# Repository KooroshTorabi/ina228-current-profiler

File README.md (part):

# INA228 current profiler: four revisions, from nanoamps to USB-C chargers

Open-hardware current and power meters built around TI's **INA228** 20-bit power monitor. They come in four revisions (A–D) for two jobs:

- **A, B, C: profiling microcontrollers** such as an STM32, from **deep sleep (tens of nA)** up to **full load (2.5 A)**. Three series shunts and two P-MOSFETs switch the measurement range.
- **D: USB-C power meter.** An in-line tester for chargers, phones and power banks (4–48 V, 5 A), with the analysis in a PC app.

**3D view of all four:** https://kourosh.site/ina228-current-profiler/viewer (buttons A–D at the top).

## The four revisions

| | A: integrated | B: module adapter | C: smart | D: USB-C power meter |
|---|---|---|---|---|
| |  |  |  |  |
| **Measures** | ~5 nA – 2.5 A, VIN up to ~6 V | ~5 nA – 2.5 A, VIN up to ~6 V | ~5 nA – 2.5 A, VIN 1.8–5.5 V | 7.8 µA steps – 5 A, 4–48 V |
| **Shunts / ranges** | 3 shunts, 3 ranges | 3 shunts, 3 ranges | 3 shunts, 3 ranges | 1 shunt (10 mΩ), 2 ADC ranges |
| **INA228** | on the board | off-the-shelf breakout (SparkFun or Adafruit) | on the board | on the board |
| **Who switches ranges** | your logger MCU | your logger MCU | the board (STM32G030 + comparator) | the board (STM32G0B1) |
| **Connects to** | logger MCU: I2C + 2 control lines | logger MCU: Qwiic I2C + 2 control lines | Pi / MCU / PC: I2C 0x48 or CSV over UART | PC: USB-C, serial port + browser app |
| **The host gets** | raw INA228 readings | raw INA228 readings | one number: A, V, charge, energy | V, A, W, mAh, Wh, CC/D± lines, reports |
| **Board** | 62 × 49 mm | 62 × 49 mm | 62 × 62 mm | 56 × 32 mm + USB-C plug |
| **Build** | JLCPCB assembled | adapter only, cheapest | JLCPCB assembled | JLCPCB assembled |
| **Files** | [`hardware/`](hardware) | [`hardware-module/`](hardware-module) · [notes](docs/module.md) | [`hardware-smart/`](hardware-smart) · [notes](docs/smart.md) · [firmware](firmware/smart) | [`hardware-usb/`](hardware-usb) · [notes](docs/usb.md) · [firmware](firmware/usb) · [app](https://kourosh.site/ina228-current-profiler/app/) |

## Which one to build

- **A: integrated.** You are building your own logger and want to write the ranging yourself.
  - Best for: battery-life studies of an STM32 or nRF board, controlled from your own firmware.
  - Not for: plugging into a PC and reading a number straight away; a logger MCU is needed.
- **B: module adapter.** You already have a SparkFun or Adafruit INA228 breakout, or don't want to solder a 0.5 mm-pitch chip.
  - Best for: the cheapest way to try range switching, a quick lab setup.
  - Not for: the best accuracy at nA; the sense wires to the breakout add noise and need care.
- **C: smart.** The host should just read a current: a Raspberry Pi, a test rig, a CI setup.
  - Best for: low-power profiling without writing ranging code: three ranges that look like one from nA to 2.5 A, plus exact charge and energy.
  - Not for: anything above 5.5 V or 2.5 A (A and B have the same current limit and reach about 6 V).
- **D: USB-C power meter.** Chargers, phones, power banks and cables, not microcontrollers.
  - Best for:
    - seeing what a charger negotiates (USB PD up to 48 V, PPS, QC, Apple, BC1.2) and logging a whole charge;
    - charger + cable resistance and an estimate of the battery's health, in the PC app.
  - Not for: sleep currents below about 10 µA (one 10 mΩ shunt) or SuperSpeed data (USB 2.0 is passed through).

Rough cost of D per assembled board at JLCPCB (parts, fees, shipping to the EU and VAT):
- about €20–25 each when 5 are ordered, €40–50 each for 2, and about $8–10 at 100+;
- A and C fall in the same range;
- B is cheaper, plus the breakout.

Most of the cost of a small order is JLC's fixed fees and shipping, not the parts.

## Details per revision

### A: integrated

- **On the board:** the INA228, the three shunts (50 mΩ, 1 Ω, 1 kΩ), the range MOSFETs Q1/Q2 and their gate drivers.
- **Your logger MCU:** reads the INA228 over I2C (0x40) and switches ranges with CTL_H / CTL_M. ALERT gives a fast interrupt for stepping up.
- **Connections:** VIN (J1) and DUT (J2) on 5.08 mm screw terminals, the logger on J3 (pinout [below](#logger-connector-j3-a)).
- Range table and principle: [How A–C work](#how-ac-work) · design notes: [docs/design.md](docs/design.md)

### B: module adapter

- **The adapter carries the ranging**: the shunts, range MOSFETs and gate drivers are on the adapter. The INA228 is on the breakout.
- **J4 is a Kelvin sense output**:
  - S+ is taken from the R1 pad, S− from the DUT terminal.
  - Wire S+ to the module's IN+, S− to IN− (and VBUS), GND to GND.
  - **No load current flows through the module.**
- **I2C:** the module's Qwiic connector goes to the logger. The adapter's J3 has only `3V3, GND, CTL_H, CTL_M`.

> **⚠ Disable the module's own shunt first.** Otherwise it sits directly across S+ and S−, almost all of the current goes through the sense wires, and every range reads wrong.
> - **SparkFun Current Sensor INA228 (SEN-31438):** open the **SHUNT** jumper on the back.
> - **Adafruit INA228 (5832):** remove the 15 mΩ shunt resistor.
>
> Before wiring, measure the resistance between the module's IN+ and IN−. It must be high (hundreds of kΩ or more), not milliohms.

Keep the S+/S− wires short (under 15 cm) and twisted, and away from the J1–J2 current path. Full preparation and wiring notes: [docs/module.md](docs/module.md).

### C: smart (on-board ranging)

- **One value out:**
  - I2C: read a `float` at register 0x04 of address 0x48.
  - UART: each line is `t_us,current_A,voltage_V,range`.
  - The board also integrates **charge and energy** at the full conversion rate. Average current between two reads = Δcharge / Δtime, exact even with slow polling.
- **Fast up-ranging in hardware:**
  - A TLV7021 comparator watches the drop across the shunts (threshold ≈ 32 mV).
  - When the DUT wakes up, it interrupts the MCU, which steps up a range in about 1 µs.
  - Down-ranging is done in firmware with hysteresis, so ranges never oscillate.
- **Supply:** VIN 1.8–5.5 V. 3V3 for the board comes from the host header.
- **Programming:** SWD pads (J4) for an ST-Link, such as the one on a Nucleo board.
- Details: [docs/smart.md](docs/smart.md) · firmware and register map: [firmware/smart](firmware/smart)

### D: USB-C power meter

- **Hardware:** a USB-C plug (J1) goes into the charger, the device's cable goes into the receptacle (J2), and a second USB-C port (J3) goes to the PC.
- **Measures:** V, A, W, mAh and mWh, plus the CC1/CC2/D+/D− line voltages (Type-C current advertisement, VCONN, QC/Apple/BC1.2 levels).
- **No display:** everything goes to the PC over USB as a serial port.
- **Range:** 10 mΩ shunt. ±4 A in 7.8 µA steps, switching automatically to ±16 A above 3.8 A. Board limit 5 A.
- **USB PD 3.1 EPR (48 V):** the INA228 (85 V) and the 51 V TVS cover it. The plug is rated 20 V, see [docs/usb.md](docs/usb.md#will-usb-pd-31-48-v-damage-it).
- **Pass-through:** CC1, CC2, D+, D−, SBU1 and SBU2 go straight through, so PD/QC negotiation and e-marked cables work as with the cable alone. SuperSpeed lines are not passed (USB 2.0 data at most).
- **Programming:** STM32G0B1 with TinyUSB, flashed over USB (ST DFU bootloader). No programmer needed.
- **PC app:** https://kourosh.site/ina228-current-profiler/app/ opens in Chrome or Edge and talks to the meter over Web Serial, with nothing to install.
  - Live V/A/W charts, and what the charger negotiates (USB PD level, PPS, QC, Apple, BC1.2).
  - A charge-session report: phases, voltage levels, charger + cable resistance, and an estimate of the battery's capacity and health.
  - A demo session; it also opens CSV logs. Source: [`docs/app/index.html`](docs/app/index.html).
- Details: [docs/usb.md](docs/usb.md) · firmware and commands: [firmware/usb](firmware/usb)

## How A–C work

```
VIN ──R1 50mΩ──●──R2 1Ω──●──R3 1kΩ──● DUT_VDD ──► STM32 (DUT)
               │ NODE_A  │ NODE_B   │
               │         └── Q2 ────┤   Q2 bypasses R3        (mid range)
               └────────── Q1 ──────┘   Q1 bypasses R2 + R3   (high range)

INA228: IN+ = VIN (R1 pad), IN- = DUT_VDD (DUT terminal)  → always measures the whole chain
```

| Range | FETs on | Total shunt | INA228 ADCRANGE | Full scale | Useful span |
|---|---|---|---|---|---|
| L | none | ≈ 1001 Ω | 1 (±40.96 mV) | ≈ 40 µA | ~5 nA – 35 µA |
| M | Q2 | ≈ 1.05 Ω | 1 (±40.96 mV) | ≈ 38 mA | 20 µA – 35 mA |
| H | Q1 | ≈ 60 mΩ | 0 (±163.84 mV) | > 2.5 A | 20 mA – 2.5 A |

Q1 bypasses R2 and R3 together, so at high current only **one** MOSFET's Rds(on) sits in the path.

### Why not just change a breakout's shunt?

A single shunt only moves the measurement window; it does not widen it:

| Single shunt | Full scale (±40.96 mV range) | 1 LSB | Good for |
|---|---|---|---|
| 15 mΩ (stock) | 2.7 A | ≈ 5 µA | run mode |
| 1 Ω | 41 mA | ≈ 78 nA | light run, stop modes |
| 1 kΩ | 41 µA | ≈ 78 pA | deep sleep only |

Measuring an STM32 from deep sleep (tens of nA) up to full load (2.5 A) takes switched ranges. B adds them in front of a ready-made breakout.

See [docs/design.md](docs/design.md) for the design notes: wake-up transients, leakage, calibration and firmware strategy.

## How D works

```
charger ──► J1 (USB-C plug) ══ R1 10 mΩ ══ J2 (USB-C receptacle) ──► cable ──► phone / device
                     │   CC1 CC2 D+ D- SBU1 SBU2 wired straight through   │
                     └── U1 INA228 (I, V) ── U2 STM32G0B1 ── J3 USB-C ──► PC (USB serial)
```

| INA228 range | Full scale | 1 LSB | Used |
|---|---|---|---|
| ADCRANGE 1 (±40.96 mV) | ±4.096 A | 7.8 µA | below 3.8 A (back below 3.0 A) |
| ADCRANGE 0 (±163.84 mV) | ±16.4 A | 31 µA | above 3.8 A |

- **Power:** U1 and U2 are powered from the PC's USB (J3), never from the device under test.
- **Line monitors:** CC1, CC2, D+ and D− are read through 1 MΩ / 1 MΩ dividers, about 2 MΩ of load on each line.
- **Ground:** the PC's ground and the charger's ground are joined on the board, as with any USB tester connected to a PC.

## 3D models

**Interactive viewer:** https://kourosh.site/ina228-current-profiler/viewer. Buttons A–D switch the board; turn it, zoom, and point at a part to see its name and value. Direct links: [`?v=integrated`](https://kourosh.site/ina228-current-profiler/viewer/index.html?v=integrated) · [`?v=module`](https://kourosh.site/ina228-current-profiler/viewer/index.html?v=module) · [`?v=smart`](https://kourosh.site/ina228-current-profiler/viewer/index.html?v=smart) · [`?v=usb`](https://kourosh.site/ina228-current-profiler/viewer/index.html?v=usb).

**STL in GitHub's own 3D viewer:** click a file and GitHub shows a rotatable model (one colour, no copper or silkscreen):
- [`hardware/3d/current_meter.stl`](hardware/3d/current_meter.stl) (A)
- [`hardware-module/3d/current_adapter.stl`](hardware-module/3d/current_adapter.stl) (B)
- [`hardware-smart/3d/current_smart.stl`](hardware-smart/3d/current_smart.stl) (C)
- [`hardware-usb/3d/current_usb.stl`](hardware-usb/3d/current_usb.stl) (D)

| A, bottom | B, bottom | C, bottom | D, bottom |
|---|---|---|---|
|  |  |  |  |

- **STEP** (`hardware*/3d/*.step`): opens in any CAD tool (FreeCAD, Fusion, SolidWorks) for enclosure design.
- **STL** (`hardware*/3d/*.stl`): one-colour mesh in mm, shown by GitHub and accepted by any slicer or mesh tool.
- **GLB** (`hardware*/3d/*.glb`): the same model with copper, solder mask and silkscreen from the real board layers. Opens in any glTF viewer (Blender, online glTF viewers).
- **Parts:** 3D bodies come from the KiCad 3D library. D's USB-C connectors have no library model, so `tools/add_usb_bodies.py` adds simple bodies for them.
- **Terminals (A–C):** the wire entries of J1 and J2 face the board edge.

## PCB

| A, top | B, top | C, top | D, top |
|---|---|---|---|
|  |  |  |  |

Bottom layers: `docs/*/pcb_bottom.svg`. Schematics: `hardware*/schematic.pdf` and `docs/*/schematic.svg`.

- **Boards:** all 2 layers, 1 oz copper, GND pour on both layers.
  - A and B: 62 × 49 mm. C: 62 × 62 mm. Both with 4 × M3 holes.
  - D: 56 × 32 mm plus the paddle that carries the USB-C plug. No holes.
- **Connectors:**
  - A–C: 5.08 mm screw terminals for VIN (J1) and DUT (J2), with the wire entries facing the board edge.
  - D: USB-C plug (in), USB-C receptacle (out), USB-C receptacle (PC).
- **Hand-routed nets (A–C):** the measurement-critical nets (VIN, NODE_A, NODE_B, DUT_VDD) are routed in `tools/gen_pcb.py` and locked:
  - The 2.5 A path is 2 mm wide.
  - IN+ / S+ is a Kelvin trace from the R1 pad.
  - IN− / S− is a Kelvin trace from the DUT terminal.
  - The gate pull-ups tap VIN upstream of the sense point.
  - C: the comparator's VIN feed and its IN+ line from DUT_VDD are hand-routed too.
- **Hand-routed nets (D)**, in `tools/gen_pcb_usb.py`:
  - The 5 A paths (VBUS_IN, VBUS_OUT) are 2 mm buses. The plug's four VBUS pins are joined through vias.
  - The Kelvin taps from R1 go to the INA228.
  - The paired VBUS and D+/D− pads of the receptacles are joined.
- **Autorouted nets:** everything else is routed with Freerouting.
- **Checks:** for every board, DRC is clean, nothing is unconnected, and every footprint is linked to its schematic symbol.
  - The one remaining DRC note on D is inside the JAE plug's own footprint: its shell pads sit about 0.2 mm from its own paddle edge.
- **Fabrication:** `fab/gerbers.zip` (Gerbers + drill) and `fab/positions_top.csv` in each hardware folder.

## Ordering assembled boards

A, C and D are ready to order fully assembled from JLCPCB: Gerbers, BOM with LCSC part numbers, and the pick-and-place file are in [`hardware/jlcpcb/`](hardware/jlcpcb), [`hardware-smart/jlcpcb/`](hardware-smart/jlcpcb) and [`hardware-usb/jlcpcb/`](hardware-usb/jlcpcb). B is a plain adapter: order the bare PCB from `hardware-module/fab/` and solder it by hand, or adapt `tools/jlcpcb.py`.

Settings, part list, fallback parts and what to check in the placement preview: [docs/ordering.md](docs/ordering.md).

**For D, before ordering:**
- Set the PCB thickness to what the JAE plug needs.
- JLC may not place J1 (pads on both layers); it can then be soldered by hand.

Both are explained in [docs/usb.md](docs/usb.md#before-ordering).

## Repository layout

```
hardware/            A: KiCad project, fab/, 3d/, jlcpcb/, schematic.pdf, BOM.csv
hardware-module/     B: same structure (no jlcpcb/)
hardware-smart/      C: same structure
hardware-usb/        D: same structure
docs/
  design.md          A–C design notes and calibration procedure
  module.md          B: preparing and wiring the breakout
  smart.md           C: on-board ranging, comparator, sample rate
  usb.md             D: USB-C power meter, PD 3.1 limits, pass-through, PC app, board notes
  ordering.md        ordering A, C and D assembled (JLCPCB)
  integrated/ module/ smart/ usb/  schematic, PCB and 3D renders
  viewer/            interactive 3D viewer (served at kourosh.site)
  app/               D's PC app: live charts and charge reports in the browser (Web Serial)
firmware/
  smart/             C firmware (STM32G030, bare metal) + host scripts for Pi / PC
  usb/               D firmware (STM32G0B1, TinyUSB CDC) + host/meter.py
tools/
  gen_schematic.py   schematic, symbol library and BOM   (arg: integrated | module | smart | usb)
  gen_pcb.py         A–C placement + hand-routing of the critical nets
  gen_pcb_usb.py     D placement, board outline with the plug paddle, 5 A paths and Kelvin taps
  route.py           Freerouting for the remaining nets, GND pours, DRC-gated retries
  step2glb.py        STEP → GLB with colours (OpenCascade)
  make_3d.py         adds copper/mask/silk textures to the GLB
  add_usb_bodies.py  simple 3D bodies for D's USB-C connectors
  render_3d.py       PNG renders of the GLB
  glb2stl.py         one-colour STL for GitHub's 3D viewer
  build_pcb.sh       runs all of the above and exports fab files
  jlcpcb.py          JLCPCB BOM + CPL for assembled boards   (arg: integrated | smart | usb)
```

## Host connections

### Logger connector (J3), A

| Pin | Signal | Notes |
|---|---|---|
| 1 | +3V3 | supplies the INA228 |
| 2 | GND | common ground with the DUT |
| 3 | SDA | INA228 at I2C address 0x40 |
| 4 | SCL | |
| 5 | ALERT | open drain; use as an interrupt for fast up-ranging |
| 6 | CTL_H | HIGH = Q1 on (high range). Pulled HIGH at reset |
| 7 | CTL_M | HIGH = Q2 on (mid range). Pulled HIGH at reset |

### B, C and D

- **B:** J3 is pins 1, 2, 6 and 7 of the list above, in that order. Its J4 is S+, S−, GND.
- **C:** J3 is `3V3, GND, SDA, SCL, TX, RX`: I2C slave 0x48 and UART 921600 8N1. See [firmware/smart](firmware/smart#host-interfaces-j3).
- **D:** J3 is a USB-C port. Use any USB-C or USB-A-to-C cable to the PC.
  - It shows up as a serial port (VID:PID 1209:0001) and needs no driver.
  - Data and commands: [firmware/usb](firmware/usb#output).

## Status

| | Schematic | PCB | 3D | JLCPCB files | Firmware | Fabricated / tested |
|---|---|---|---|---|---|---|
| A | ✓ | ✓ | ✓ | ✓ | logger firmware not written yet | not yet |
| B | ✓ | ✓ | ✓ | (bare PCB) | same as A | not yet |
| C | ✓ | ✓ | ✓ | ✓ | ✓ compiles, not yet run | not yet |
| D | ✓ | ✓ | ✓ | ✓ | ✓ compiles, not yet run · PC app tested with its demo | not yet |

Open work: logger firmware for A/B, and calibration and validation of every revision against a reference meter.

## Rebuilding

The schematics, PCBs and 3D files are all generated from scripts:

```sh
# needs KiCad 7+ with footprint and 3D libraries, Java, xvfb-run and the Freerouting 1.9 jar;
# the 3D step also needs: pip install cadquery-ocp trimesh pillow pyrender "pyopengl==3.1.7"
tools/build_pcb.sh /path/to/freerouting-1.9.0.jar integrated   # A
tools/build_pcb.sh /path/to/freerouting-1.9.0.jar module       # B
tools/build_pcb.sh /path/to/freerouting-1.9.0.jar smart        # C
tools/build_pcb.sh /path/to/freerouting-1.9.0.jar usb          # D
python3 tools/jlcpcb.py integrated     # JLCPCB BOM + CPL for A
python3 tools/jlcpcb.py smart          # ... for C
python3 tools/jlcpcb.py usb            # ... for D
make -C firmware/smart                 # C firmware (arm-none-eabi-gcc)
make -C firmware/usb                   # D firmware (fetches TinyUSB 0.18.0 with git)
```

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
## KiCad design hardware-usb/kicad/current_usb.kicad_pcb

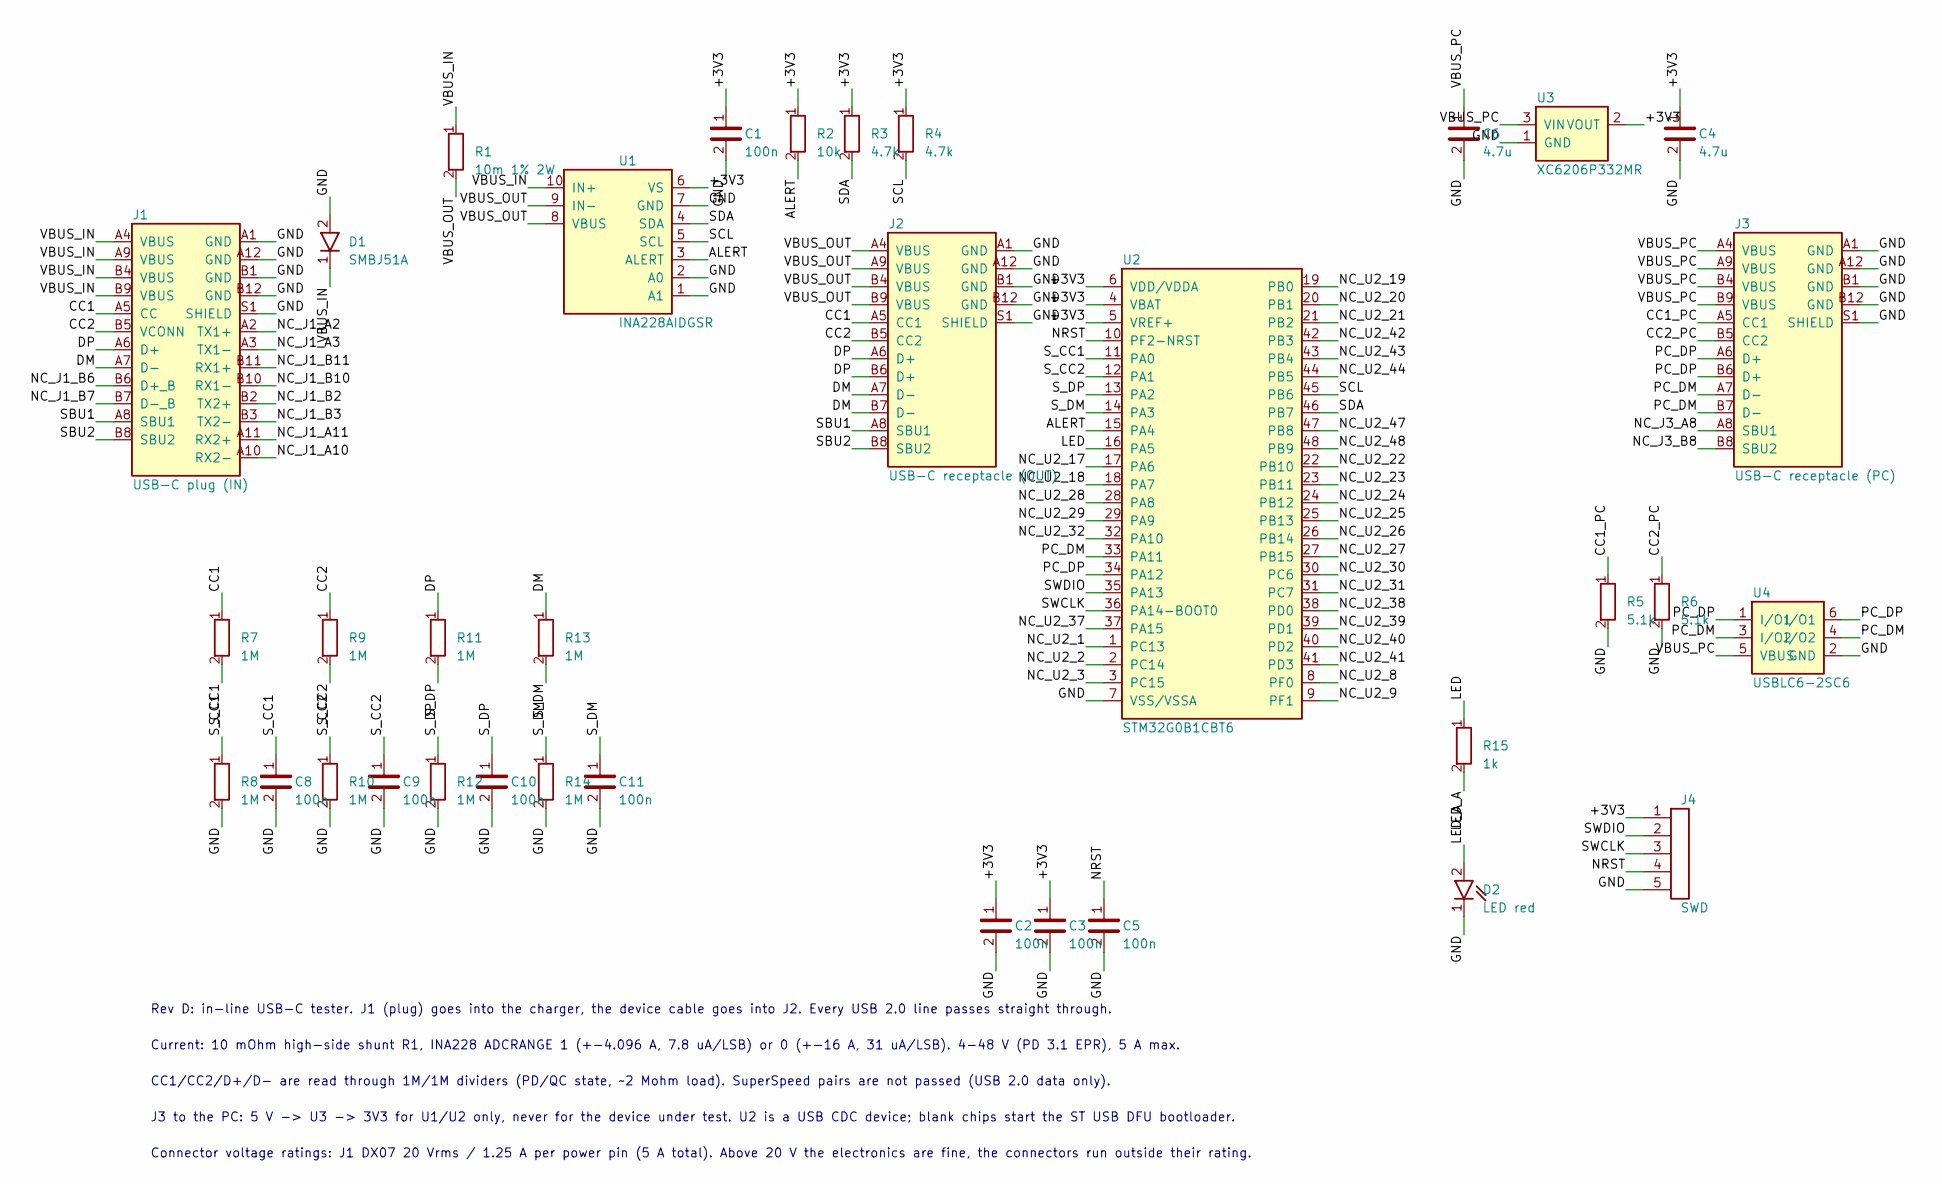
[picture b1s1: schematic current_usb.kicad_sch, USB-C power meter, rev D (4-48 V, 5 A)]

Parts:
C1, C2, C3, C5, C8, C9, C10, C11: 100n; C_0603_1608Metric
C4, C6: 4.7u; C_0603_1608Metric
D1: SMBJ51A; D_SMB
D2: LED red; LED_0603_1608Metric
J1: USB-C plug (IN); USB_C_Plug_JAE_DX07P024AJ1
J2: USB-C receptacle (OUT); USB_C_Receptacle_HRO_TYPE-C-31-M-12
J3: USB-C receptacle (PC); USB_C_Receptacle_HRO_TYPE-C-31-M-12
J4: SWD; PinHeader_1x05_P1.27mm_Vertical
R1: 10m 1% 2W; R_2512_6332Metric
R2: 10k; R_0603_1608Metric
R3, R4: 4.7k; R_0603_1608Metric
R5, R6: 5.1k; R_0603_1608Metric
R7, R8, R9, R10, R11, R12, R13, R14: 1M; R_0603_1608Metric
R15: 1k; R_0603_1608Metric
U1: INA228AIDGSR; VSSOP-10_3x3mm_P0.5mm
U2: STM32G0B1CBT6; LQFP-48_7x7mm_P0.5mm
U3: XC6206P332MR; SOT-23
U4: USBLC6-2SC6; SOT-23-6

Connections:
+3V3: C1.1, C2.1, C3.1, C4.1, J4.1, R2.1, R3.1, R4.1, U1.6 (VS), U2.4 (VBAT), U2.5 (VREF+), U2.6 (VDD/VDDA), U3.2 (VOUT)
ALERT: R2.2, U1.3 (ALERT), U2.15 (PA4)
CC1: J1.A5 (CC), J2.A5 (CC1), R7.1
CC1_PC: J3.A5 (CC1), R5.1
CC2: J1.B5 (VCONN), J2.B5 (CC2), R9.1
CC2_PC: J3.B5 (CC2), R6.1
DM: J1.A7 (D-), J2.A7 (D-), J2.B7 (D-), R13.1
DP: J1.A6 (D+), J2.A6 (D+), J2.B6 (D+), R11.1
GND: C1.2, C2.2, C3.2, C4.2, C5.2, C6.2, C8.2, C9.2, C10.2, C11.2, D1.2 (A), D2.1 (K), J1.A1 (GND), J1.A12 (GND), J1.B1 (GND), J1.B12 (GND), J1.S1 (SHIELD), J2.A1 (GND), J2.A12 (GND), J2.B1 (GND), J2.B12 (GND), J2.S1 (SHIELD), J3.A1 (GND), J3.A12 (GND), J3.B1 (GND), J3.B12 (GND), J3.S1 (SHIELD), J4.5, R5.2, R6.2, R8.2, R10.2, R12.2, R14.2, U1.1 (A1), U1.2 (A0), U1.7 (GND), U2.7 (VSS/VSSA), U3.1 (GND), U4.2 (GND)
LED: R15.1, U2.16 (PA5)
LED_A: D2.2 (A), R15.2
NC_J1_A2: J1.A2 (TX1+)
NC_J1_A3: J1.A3 (TX1-)
NC_J1_A10: J1.A10 (RX2-)
NC_J1_A11: J1.A11 (RX2+)
NC_J1_B2: J1.B2 (TX2+)
NC_J1_B3: J1.B3 (TX2-)
NC_J1_B6: J1.B6 (D+_B)
NC_J1_B7: J1.B7 (D-_B)
NC_J1_B10: J1.B10 (RX1-)
NC_J1_B11: J1.B11 (RX1+)
NC_J3_A8: J3.A8 (SBU1)
NC_J3_B8: J3.B8 (SBU2)
NC_U2_1: U2.1 (PC13)
NC_U2_2: U2.2 (PC14)
NC_U2_3: U2.3 (PC15)
NC_U2_8: U2.8 (PF0)
NC_U2_9: U2.9 (PF1)
NC_U2_17: U2.17 (PA6)
NC_U2_18: U2.18 (PA7)
NC_U2_19: U2.19 (PB0)
NC_U2_20: U2.20 (PB1)
NC_U2_21: U2.21 (PB2)
NC_U2_22: U2.22 (PB10)
NC_U2_23: U2.23 (PB11)
NC_U2_24: U2.24 (PB12)
NC_U2_25: U2.25 (PB13)
NC_U2_26: U2.26 (PB14)
NC_U2_27: U2.27 (PB15)
NC_U2_28: U2.28 (PA8)
NC_U2_29: U2.29 (PA9)
NC_U2_30: U2.30 (PC6)
NC_U2_31: U2.31 (PC7)
NC_U2_32: U2.32 (PA10)
NC_U2_37: U2.37 (PA15)
NC_U2_38: U2.38 (PD0)
NC_U2_39: U2.39 (PD1)
NC_U2_40: U2.40 (PD2)
NC_U2_41: U2.41 (PD3)
NC_U2_42: U2.42 (PB3)
NC_U2_43: U2.43 (PB4)
NC_U2_44: U2.44 (PB5)
NC_U2_47: U2.47 (PB8)
NC_U2_48: U2.48 (PB9)
NRST: C5.1, J4.4, U2.10 (PF2-NRST)
PC_DM: J3.A7 (D-), J3.B7 (D-), U2.33 (PA11), U4.3 (I/O2), U4.4 (I/O2)
PC_DP: J3.A6 (D+), J3.B6 (D+), U2.34 (PA12), U4.1 (I/O1), U4.6 (I/O1)
SBU1: J1.A8 (SBU1), J2.A8 (SBU1)
SBU2: J1.B8 (SBU2), J2.B8 (SBU2)
SCL: R4.2, U1.5 (SCL), U2.45 (PB6)
SDA: R3.2, U1.4 (SDA), U2.46 (PB7)
SWCLK: J4.3, U2.36 (PA14-BOOT0)
SWDIO: J4.2, U2.35 (PA13)
S_CC1: C8.1, R7.2, R8.1, U2.11 (PA0)
S_CC2: C9.1, R9.2, R10.1, U2.12 (PA1)
S_DM: C11.1, R13.2, R14.1, U2.14 (PA3)
S_DP: C10.1, R11.2, R12.1, U2.13 (PA2)
VBUS_IN: D1.1 (K), J1.A4 (VBUS), J1.A9 (VBUS), J1.B4 (VBUS), J1.B9 (VBUS), R1.1, U1.10 (IN+)
VBUS_OUT: J2.A4 (VBUS), J2.A9 (VBUS), J2.B4 (VBUS), J2.B9 (VBUS), R1.2, U1.8 (VBUS), U1.9 (IN-)
VBUS_PC: C6.1, J3.A4 (VBUS), J3.A9 (VBUS), J3.B4 (VBUS), J3.B9 (VBUS), U3.3 (VIN), U4.5 (VBUS)

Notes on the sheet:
Rev D: in-line USB-C tester. J1 (plug) goes into the charger, the device cable goes into J2. Every USB 2.0 line passes straight through.
Current: 10 mOhm high-side shunt R1, INA228 ADCRANGE 1 (+-4.096 A, 7.8 uA/LSB) or 0 (+-16 A, 31 uA/LSB). 4-48 V (PD 3.1 EPR), 5 A max.
CC1/CC2/D+/D- are read through 1M/1M dividers (PD/QC state, ~2 Mohm load). SuperSpeed pairs are not passed (USB 2.0 data only).
J3 to the PC: 5 V -> U3 -> 3V3 for U1/U2 only, never for the device under test. U2 is a USB CDC device; blank chips start the ST USB DFU bootloader.
Connector voltage ratings: J1 DX07 20 Vrms / 1.25 A per power pin (5 A total). Above 20 V the electronics are fine, the connectors run outside their rating.

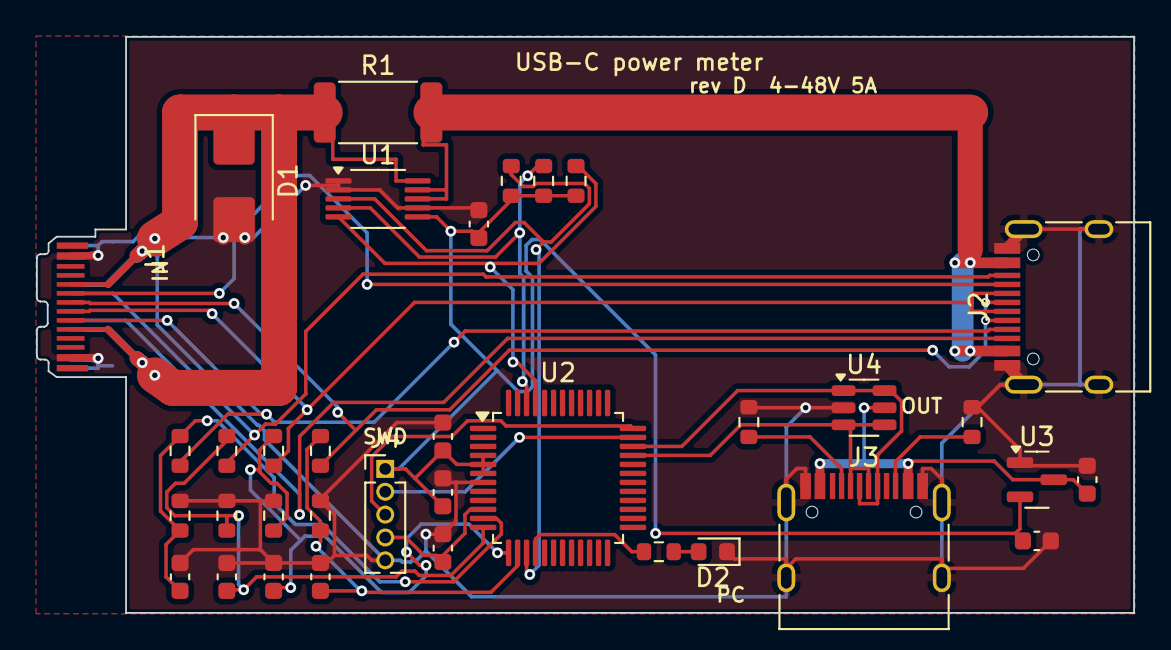
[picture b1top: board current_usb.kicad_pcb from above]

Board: 2 copper layers, 61.0 x 32.0 mm, 35 parts (0 on the bottom side), 27 nets.

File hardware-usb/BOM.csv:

Ref,Value,Footprint,Note
J1,USB-C plug (IN),Connector_USB:USB_C_Plug_JAE_DX07P024AJ1,"Input: plugs into the charger. Pass-through pin to pin, like a short extension."
J2,USB-C receptacle (OUT),Connector_USB:USB_C_Receptacle_HRO_TYPE-C-31-M-12,Output: the phone / device cable plugs in here. CC1/CC2/D+/D-/SBU wired straight to J1.
R1,10m 1% 2W,Resistor_SMD:R_2512_6332Metric,"Shunt, high side, Kelvin taps to U1"
D1,SMBJ51A,Diode_SMD:D_SMB,"TVS: 51 V stand-off (PD 3.1 EPR 48 V), clamps below the INA228 85 V limit"
U1,INA228AIDGSR,Package_SO:VSSOP-10_3x3mm_P0.5mm,"I2C 0x40. Measures bus V on the OUT side, 0-85 V"
C1,100n,Capacitor_SMD:C_0603_1608Metric,U1 VS decoupling
R2,10k,Resistor_SMD:R_0603_1608Metric,ALERT open-drain pull-up
R3,4.7k,Resistor_SMD:R_0603_1608Metric,I2C pull-up
R4,4.7k,Resistor_SMD:R_0603_1608Metric,I2C pull-up
R7,1M,Resistor_SMD:R_0603_1608Metric,"CC1 monitor divider, top"
R8,1M,Resistor_SMD:R_0603_1608Metric,"CC1 monitor divider, bottom"
C8,100n,Capacitor_SMD:C_0603_1608Metric,CC1 monitor filter
R9,1M,Resistor_SMD:R_0603_1608Metric,"CC2 monitor divider, top"
R10,1M,Resistor_SMD:R_0603_1608Metric,"CC2 monitor divider, bottom"
C9,100n,Capacitor_SMD:C_0603_1608Metric,CC2 monitor filter
R11,1M,Resistor_SMD:R_0603_1608Metric,"DP monitor divider, top"
R12,1M,Resistor_SMD:R_0603_1608Metric,"DP monitor divider, bottom"
C10,100n,Capacitor_SMD:C_0603_1608Metric,DP monitor filter
R13,1M,Resistor_SMD:R_0603_1608Metric,"DM monitor divider, top"
R14,1M,Resistor_SMD:R_0603_1608Metric,"DM monitor divider, bottom"
C11,100n,Capacitor_SMD:C_0603_1608Metric,DM monitor filter
J3,USB-C receptacle (PC),Connector_USB:USB_C_Receptacle_HRO_TYPE-C-31-M-12,"To the PC: USB 2.0 full speed (CDC serial), 5 V supply for the meter only"
R5,5.1k,Resistor_SMD:R_0603_1608Metric,Rd: PC sees a USB device
R6,5.1k,Resistor_SMD:R_0603_1608Metric,Rd
U4,USBLC6-2SC6,Package_TO_SOT_SMD:SOT-23-6,ESD on the PC port
U3,XC6206P332MR,Package_TO_SOT_SMD:SOT-23,3.3 V LDO from PC USB 5 V
C6,4.7u,Capacitor_SMD:C_0603_1608Metric,LDO input
C4,4.7u,Capacitor_SMD:C_0603_1608Metric,LDO output / 3V3 bulk
U2,STM32G0B1CBT6,Package_QFP:LQFP-48_7x7mm_P0.5mm,"USB FS device (crystal-less, CRS on SOF), I2C1 = INA228, ADC = CC/D+/D- monitors. Ships with USB DFU bootloader."
C2,100n,Capacitor_SMD:C_0603_1608Metric,U2 VDD decoupling
C3,100n,Capacitor_SMD:C_0603_1608Metric,U2 VBAT/VREF+ decoupling
C5,100n,Capacitor_SMD:C_0603_1608Metric,NRST filter
R15,1k,Resistor_SMD:R_0603_1608Metric,status LED resistor
D2,LED red,LED_SMD:LED_0603_1608Metric,status LED
J4,SWD,Connector_PinHeader_1.27mm:PinHeader_1x05_P1.27mm_Vertical,Optional SWD (not assembled; USB DFU is enough)

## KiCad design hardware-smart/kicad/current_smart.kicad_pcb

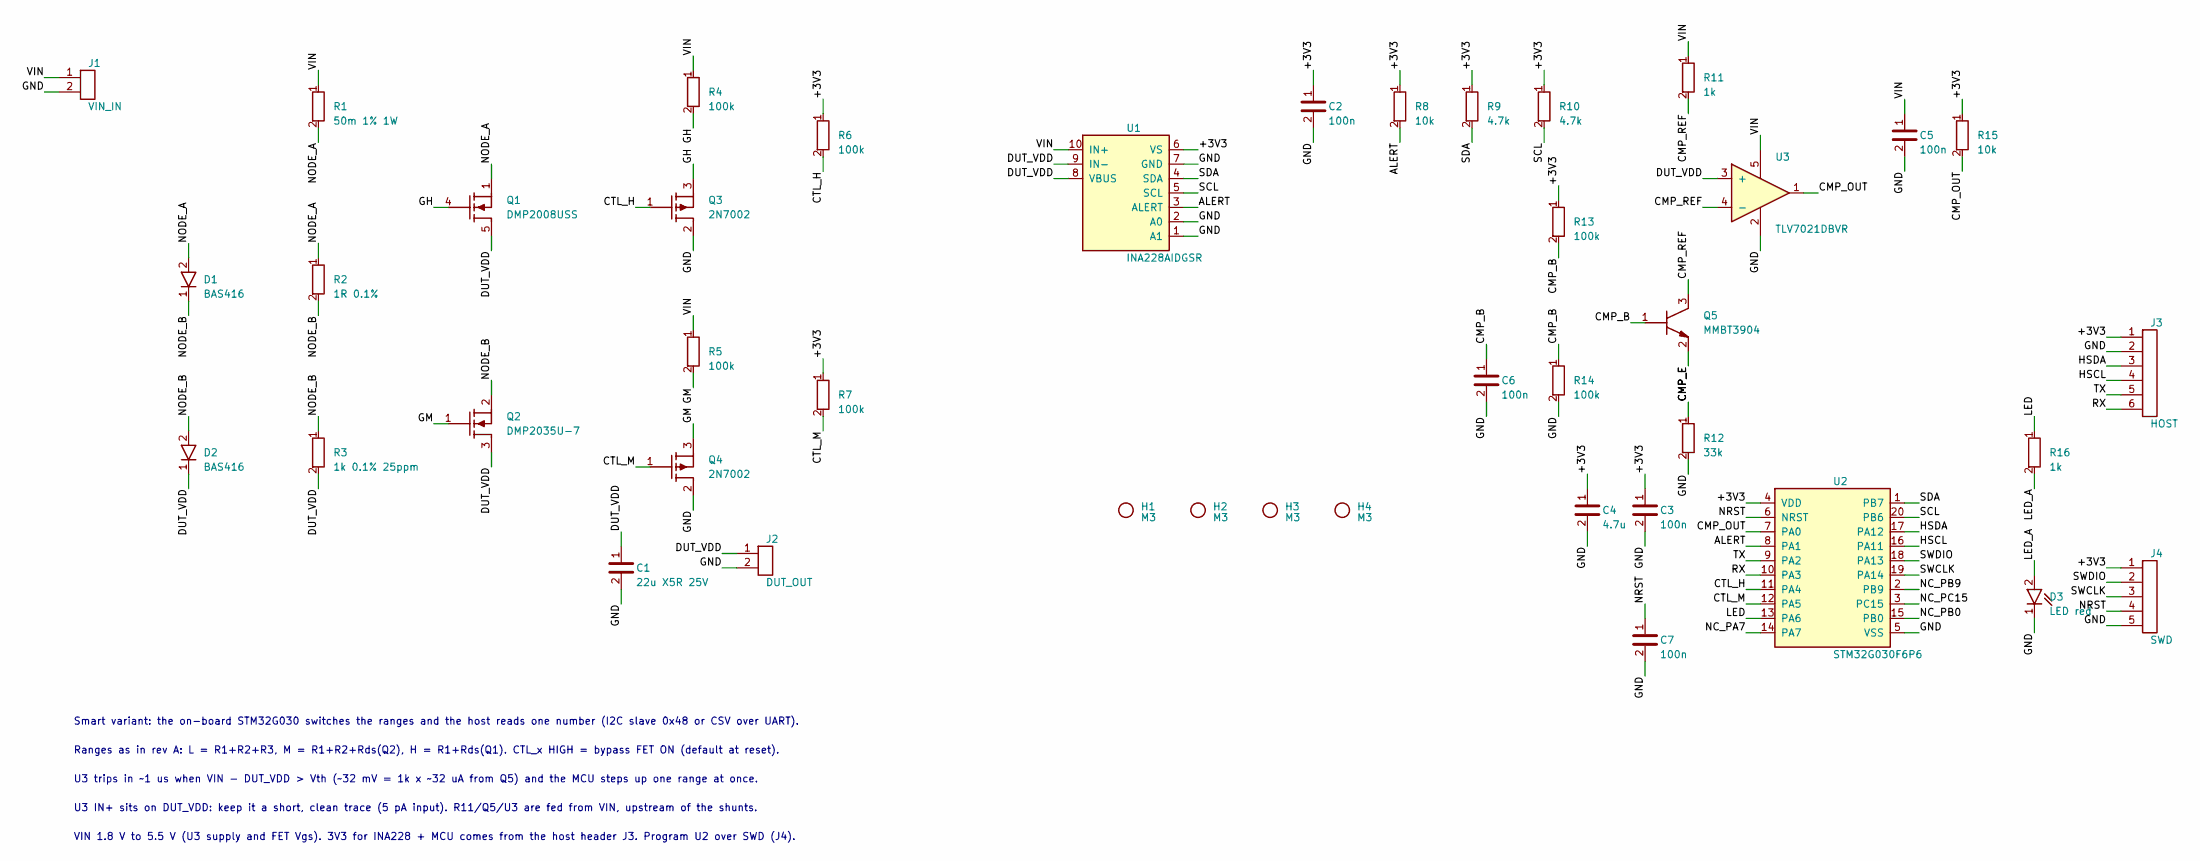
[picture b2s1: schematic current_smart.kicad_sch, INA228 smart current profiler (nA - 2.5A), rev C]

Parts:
C1: 22u X5R 25V; C_1206_3216Metric
C2, C3, C5, C6, C7: 100n; C_0603_1608Metric
C4: 4.7u; C_0603_1608Metric
D1, D2: BAS416; D_SOD-323
D3: LED red; LED_0603_1608Metric
H1, H2, H3, H4: M3; MountingHole_3.2mm_M3
J1: VIN_IN; TerminalBlock_Phoenix_MKDS-1,5-2-5.08_1x02_P5.08mm_Horizont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
J2: DUT_OUT; TerminalBlock_Phoenix_MKDS-1,5-2-5.08_1x02_P5.08mm_Horizont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
J3: HOST; PinHeader_1x06_P2.54mm_Vertical
J4: SWD; PinHeader_1x05_P2.54mm_Vertical
Q1: DMP2008USS; SOIC-8_3.9x4.9mm_P1.27mm
Q2: DMP2035U-7; SOT-23
Q3, Q4: 2N7002; SOT-23
Q5: MMBT3904; SOT-23
R1: 50m 1% 1W; R_2512_6332Metric
R2: 1R 0.1%; R_1206_3216Metric
R3: 1k 0.1% 25ppm; R_0805_2012Metric
R4, R5, R6, R7, R13, R14: 100k; R_0603_1608Metric
R8, R15: 10k; R_0603_1608Metric
R9, R10: 4.7k; R_0603_1608Metric
R11, R16: 1k; R_0603_1608Metric
R12: 33k; R_0603_1608Metric
U1: INA228AIDGSR; VSSOP-10_3x3mm_P0.5mm
U2: STM32G030F6P6; TSSOP-20_4.4x6.5mm_P0.65mm
U3: TLV7021DBVR; SOT-23-5

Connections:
+3V3: C2.1, C3.1, C4.1, J3.1, J4.1, R6.1, R7.1, R8.1, R9.1, R10.1, R13.1, R15.1, U1.6 (VS), U2.4 (VDD)
ALERT: R8.2, U1.3 (ALERT), U2.8 (PA1)
CMP_B: C6.1, Q5.1 (B), R13.2, R14.1
CMP_E: Q5.2 (E), R12.1
CMP_OUT: R15.2, U2.7 (PA0), U3.1
CMP_REF: Q5.3 (C), R11.2, U3.4 (-)
CTL_H: Q3.1 (G), R6.2, U2.11 (PA4)
CTL_M: Q4.1 (G), R7.2, U2.12 (PA5)
DUT_VDD: C1.1, D2.1 (K), J2.1, Q1.5 (D), Q1.6 (D), Q1.7 (D), Q1.8 (D), Q2.3 (D), R3.2, U1.8 (VBUS), U1.9 (IN-), U3.3 (+)
GH: Q1.4 (G), Q3.3 (D), R4.2
GM: Q2.1 (G), Q4.3 (D), R5.2
GND: C1.2, C2.2, C3.2, C4.2, C5.2, C6.2, C7.2, D3.1 (K), J1.2, J2.2, J3.2, J4.5, Q3.2 (S), Q4.2 (S), R12.2, R14.2, U1.1 (A1), U1.2 (A0), U1.7 (GND), U2.5 (VSS), U3.2
HSCL: J3.4, U2.16 (PA11)
HSDA: J3.3, U2.17 (PA12)
LED: R16.1, U2.13 (PA6)
LED_A: D3.2 (A), R16.2
NC_PA7: U2.14 (PA7)
NC_PB0: U2.15 (PB0)
NC_PB9: U2.2 (PB9)
NC_PC15: U2.3 (PC15)
NODE_A: D1.2 (A), Q1.1 (S), Q1.2 (S), Q1.3 (S), R1.2, R2.1
NODE_B: D1.1 (K), D2.2 (A), Q2.2 (S), R2.2, R3.1
NRST: C7.1, J4.4, U2.6 (NRST)
RX: J3.6, U2.10 (PA3)
SCL: R10.2, U1.5 (SCL), U2.20 (PB6)
SDA: R9.2, U1.4 (SDA), U2.1 (PB7)
SWCLK: J4.3, U2.19 (PA14)
SWDIO: J4.2, U2.18 (PA13)
TX: J3.5, U2.9 (PA2)
VIN: C5.1, J1.1, R1.1, R4.1, R5.1, R11.1, U1.10 (IN+), U3.5

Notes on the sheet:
Smart variant: the on-board STM32G030 switches the ranges and the host reads one number (I2C slave 0x48 or CSV over UART).
Ranges as in rev A: L = R1+R2+R3, M = R1+R2+Rds(Q2), H = R1+Rds(Q1). CTL_x HIGH = bypass FET ON (default at reset).
U3 trips in ~1 us when VIN - DUT_VDD > Vth (~32 mV = 1k x ~32 uA from Q5) and the MCU steps up one range at once.
U3 IN+ sits on DUT_VDD: keep it a short, clean trace (5 pA input). R11/Q5/U3 are fed from VIN, upstream of the shunts.
VIN 1.8 V to 5.5 V (U3 supply and FET Vgs). 3V3 for INA228 + MCU comes from the host header J3. Program U2 over SWD (J4).

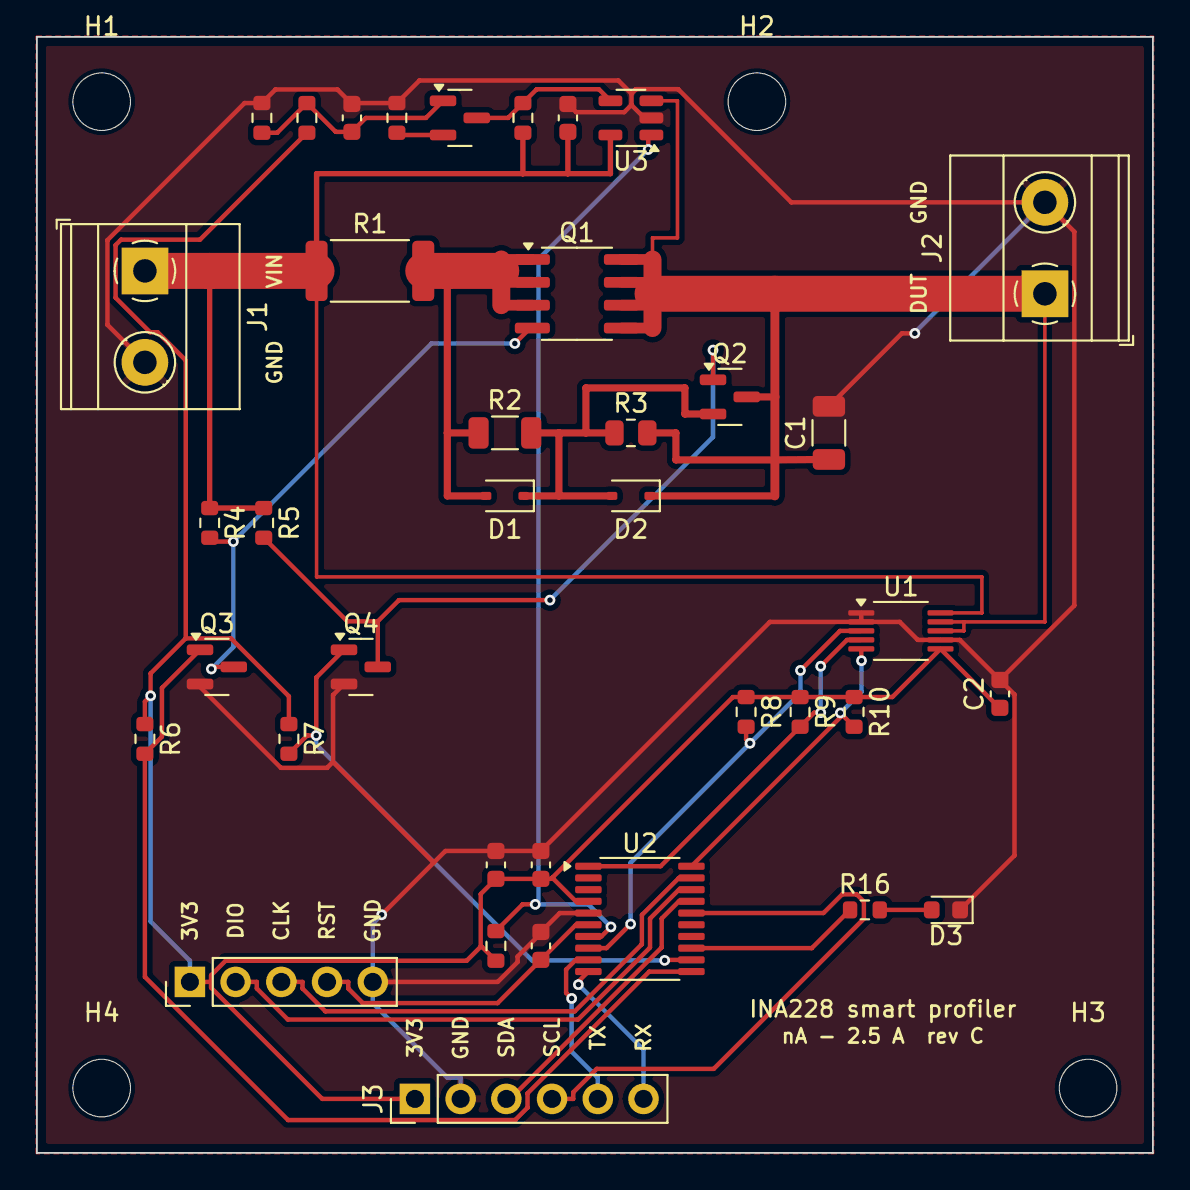
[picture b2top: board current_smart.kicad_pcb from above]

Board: 2 copper layers, 62.0 x 62.0 mm, 42 parts (0 on the bottom side), 26 nets.

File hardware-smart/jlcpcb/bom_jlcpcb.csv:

Comment,Designator,Footprint,LCSC Part #
Samsung CL31A226KAHNNNE 22µF 25V X5R,C1,1206,C12891
YAGEO CC0603KRX7R9BB104 100nF 50V X7R,"C2,C3,C5,C6,C7",0603,C14663
Samsung CL10A475KO8NNNC 4.7µF 16V X5R,C4,0603,C19666
Nexperia BAS416Z,"D1,D2",SOD-323,C549240
KENTO KT-0603R red LED,D3,0603,C2286
KEFA KF128-5.08-2P-AA screw terminal,"J1,J2",THT 5.08mm 2P,C474952
XFCN PZ254V-11-06P pin header,J3,THT 2.54mm 1x6,C492405
onsemi FDS4465 (DMP2008USS-13 alt.),Q1,SO-8,C92137
Diodes DMP2035U-7,Q2,SOT-23,C110499
JSCJ 2N7002,"Q3,Q4",SOT-23,C8545
MMBT3904,Q5,SOT-23,C20526
FORT CUM2512-24FR050 50mΩ 1% 2W,R1,2512,C323779
YAGEO 1206 1Ω 0.1% thin film,R2,1206,C2912606
YAGEO AT0805BRD071KL 1kΩ 0.1% 25ppm,R3,0805,C856765
100kΩ 1% 0603,"R4,R5,R6,R7,R13,R14",0603,C25803
10kΩ 1% 0603,"R8,R15",0603,C25804
4.7kΩ 1% 0603,"R9,R10",0603,C23162
1kΩ 1% 0603,"R11,R16",0603,C21190
33kΩ 1% 0603,R12,0603,C4216
TI INA228AIDGSR,U1,VSSOP-10,C2887910
ST STM32G030F6P6,U2,TSSOP-20,C724040
TI TLV7021DBVR comparator,U3,SOT-23-5,C2860939

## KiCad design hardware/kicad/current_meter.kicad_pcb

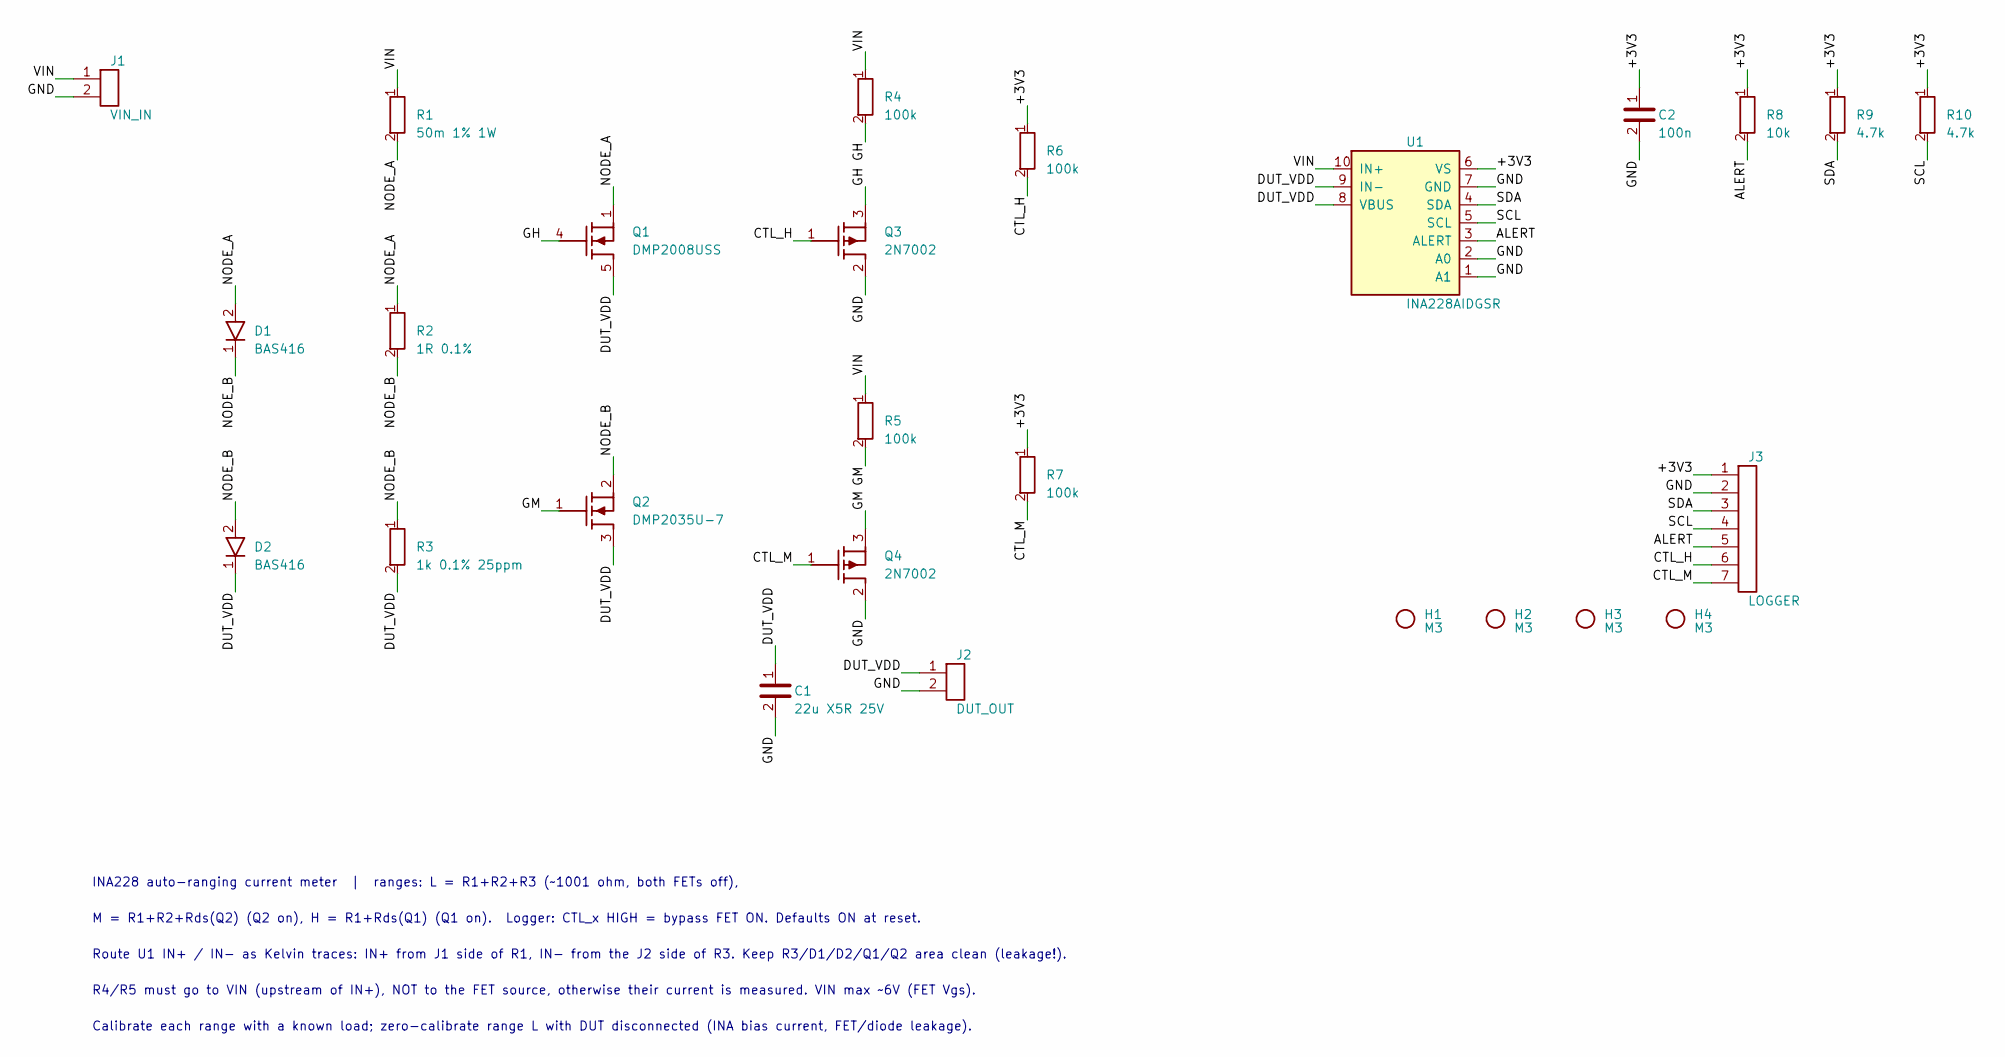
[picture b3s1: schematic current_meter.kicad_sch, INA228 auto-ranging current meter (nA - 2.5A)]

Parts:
C1: 22u X5R 25V; C_1206_3216Metric
C2: 100n; C_0603_1608Metric
D1, D2: BAS416; D_SOD-323
H1, H2, H3, H4: M3; MountingHole_3.2mm_M3
J1: VIN_IN; TerminalBlock_Phoenix_MKDS-1,5-2-5.08_1x02_P5.08mm_Horizont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
J2: DUT_OUT; TerminalBlock_Phoenix_MKDS-1,5-2-5.08_1x02_P5.08mm_Horizont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
J3: LOGGER; PinHeader_1x07_P2.54mm_Vertical
Q1: DMP2008USS; SOIC-8_3.9x4.9mm_P1.27mm
Q2: DMP2035U-7; SOT-23
Q3, Q4: 2N7002; SOT-23
R1: 50m 1% 1W; R_2512_6332Metric
R2: 1R 0.1%; R_1206_3216Metric
R3: 1k 0.1% 25ppm; R_0805_2012Metric
R4, R5, R6, R7: 100k; R_0603_1608Metric
R8: 10k; R_0603_1608Metric
R9, R10: 4.7k; R_0603_1608Metric
U1: INA228AIDGSR; VSSOP-10_3x3mm_P0.5mm

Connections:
+3V3: C2.1, J3.1, R6.1, R7.1, R8.1, R9.1, R10.1, U1.6 (VS)
ALERT: J3.5, R8.2, U1.3 (ALERT)
CTL_H: J3.6, Q3.1 (G), R6.2
CTL_M: J3.7, Q4.1 (G), R7.2
DUT_VDD: C1.1, D2.1 (K), J2.1, Q1.5 (D), Q1.6 (D), Q1.7 (D), Q1.8 (D), Q2.3 (D), R3.2, U1.8 (VBUS), U1.9 (IN-)
GH: Q1.4 (G), Q3.3 (D), R4.2
GM: Q2.1 (G), Q4.3 (D), R5.2
GND: C1.2, C2.2, J1.2, J2.2, J3.2, Q3.2 (S), Q4.2 (S), U1.1 (A1), U1.2 (A0), U1.7 (GND)
NODE_A: D1.2 (A), Q1.1 (S), Q1.2 (S), Q1.3 (S), R1.2, R2.1
NODE_B: D1.1 (K), D2.2 (A), Q2.2 (S), R2.2, R3.1
SCL: J3.4, R10.2, U1.5 (SCL)
SDA: J3.3, R9.2, U1.4 (SDA)
VIN: J1.1, R1.1, R4.1, R5.1, U1.10 (IN+)

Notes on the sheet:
INA228 auto-ranging current meter | ranges: L = R1+R2+R3 (~1001 ohm, both FETs off),
M = R1+R2+Rds(Q2) (Q2 on), H = R1+Rds(Q1) (Q1 on). Logger: CTL_x HIGH = bypass FET ON. Defaults ON at reset.
Route U1 IN+ / IN- as Kelvin traces: IN+ from J1 side of R1, IN- from the J2 side of R3. Keep R3/D1/D2/Q1/Q2 area clean (leakage!).
R4/R5 must go to VIN (upstream of IN+), NOT to the FET source, otherwise their current is measured. VIN max ~6V (FET Vgs).
Calibrate each range with a known load; zero-calibrate range L with DUT disconnected (INA bias current, FET/diode leakage).

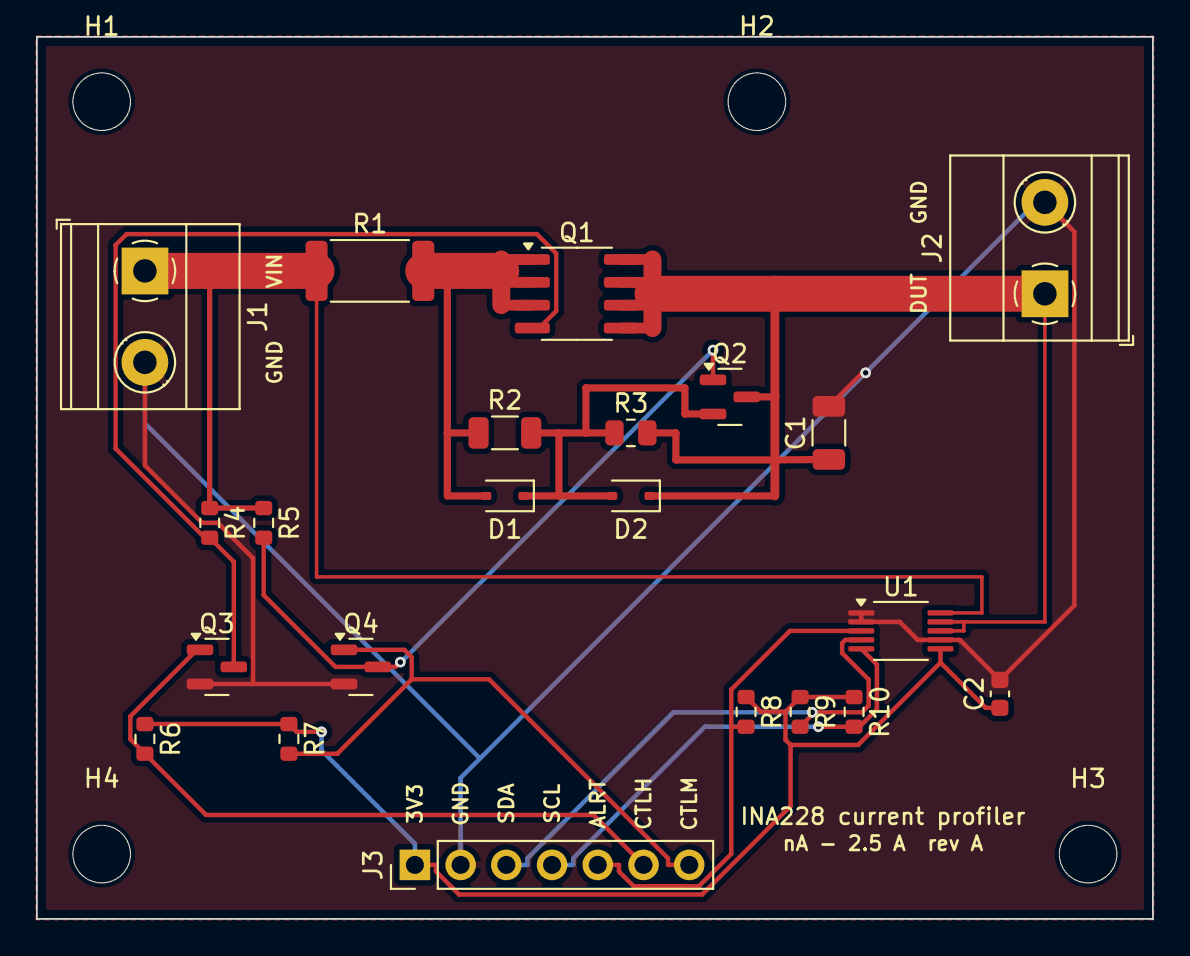
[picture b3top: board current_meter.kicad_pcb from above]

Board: 2 copper layers, 62.0 x 49.0 mm, 26 parts (0 on the bottom side), 13 nets.

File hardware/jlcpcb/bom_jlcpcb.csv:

Comment,Designator,Footprint,LCSC Part #
Samsung CL31A226KAHNNNE 22µF 25V X5R,C1,1206,C12891
YAGEO CC0603KRX7R9BB104 100nF 50V X7R,C2,0603,C14663
Nexperia BAS416Z,"D1,D2",SOD-323,C549240
KEFA KF128-5.08-2P-AA screw terminal,"J1,J2",THT 5.08mm 2P,C474952
XFCN PZ254V-11-07P pin header,J3,THT 2.54mm 1x7,C492406
Diodes DMP2008USS-13,Q1,SO-8,C6934873
Diodes DMP2035U-7,Q2,SOT-23,C110499
JSCJ 2N7002,"Q3,Q4",SOT-23,C8545
FORT CUM2512-24FR050 50mΩ 1% 2W,R1,2512,C323779
YAGEO RT1206BRD071RL 1Ω 0.1% 25ppm,R2,1206,C513714
YAGEO AT0805BRD071KL 1kΩ 0.1% 25ppm,R3,0805,C856765
100kΩ 1% 0603,"R4,R5,R6,R7",0603,C25803
10kΩ 1% 0603,R8,0603,C25804
4.7kΩ 1% 0603,"R9,R10",0603,C23162
TI INA228AIDGSR,U1,VSSOP-10,C2887910

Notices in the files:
README.md:
License:
MIT, see [LICENSE](LICENSE).
